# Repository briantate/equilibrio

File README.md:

# equilibrio
A ball balancing project

# Goals:
This is a learning project focused on several learning goals:
* State Space control theory
    * I will start with a simple PID controller, but move to state space control
* Zephyr OS
    * Investigate the west build system 
    * Create a custom board within Zephyr
    * 
* Cloud Connectivity
    * send ball position and other meta data to the cloud
    * Change the balls balancing location from the cloud
    * AWS IoT for the first iteration

# Future goals:
In the future, the following technologies may be added for learning:
* BLE
* Display/graphics
* Capacitive Touch may be investigated as a sensor for ball position

# Block diagram:

# Firmware Architecture:

# Hardware needed:
* Electronics:
    * Adafruit Metro M4 board (later to be a custom board)
    * Custom shield with headers for servo motors, touchscreen sensor, and UART header for console I/O
    * CMSIS-DAP programmer - I'm using Atmel-ICE
    * 2 MG995 180 degree metal gear servo motors
    * 2 Aluminum 25T Servo Horn Steering Arms
    * 2 RC Aluminum Linkages for Servo
    * 1 VSDISPLAY 8.4" 4 wire resistive touchscreen
* Custom balance table hardware
    * 3d-printed table hardware
    * Wooden base board to mount the table hardware

# Zephyr commands needed:
* Install the zephyr ecosystem for your OS following https://docs.zephyrproject.org/latest/develop/getting_started/index.html
* Build: need to be in the embedded_src directory
    > west build -b metro_m4 -p always -- -DBOARD_ROOT=.
    - the -DBOARD_ROOT=. tells west to look for the custom board I created in the current directory (which has the boards subdirectory)
* Flash:
    > west flash

# Notes about design choices:
* Servo:
    * I started with DS-S006L servo’s with plastic gears and plastic steering arms. These seem to work fine, but there is a lot of play in the coupling. Also, the steering arms are not very durable and split with the screws provided
    * I changed out MG995 servo’s with metal gears and steering arms. Hopefully this will reduce some of the play

* Sensor:
    * I'm using a VSDISPLAY 8.4" (172mm x 129.5mm touch area) 4-wire resistive Touch Panel I found on Amazon. I’m looking for larger (and square shaped) panels, but they get expensive quickly with increasing size
        * How 
    * When using an non-square panel, the sensor gains are different in the x and y directions. This is because the voltage drop is across a different distance in each direction, but the ADC range is the same. Ex:
        * 12b ADC = 4096 counts
        * x → 164mm/4096counts = 0.04004mm/count
        * y → 105mm/4096counts = 0x02563mm/count
    * MCU Pin voltage driving the panel lower than 3.3V:
        * The panel resistance is in the range of 300-700 ohms depending on the direction. Typical code examples for Arduino and other platforms drive this sensor with GPIO pins. This is a too much current draw for a typical GPIO pin, so the pin output voltage will drop. You can typically increase the drive strength of a GPIO, but make sure it is enough drive the load or you will measure lower voltages than expected. Ex:
            * typical default drive strength of a MCU GPIO is about 2mA
                * Max load → r=v/i = 1,650 ohms
                * at 300 ohms and 3.3V, → i=v/r = 11mA !!!
                * output pin voltage will droop to where it can actually drive this load
                * v = ir = 0.6V
    * Seeing a strange offset in the sensor reading when no touch is present:
        * The panel some capacitance between the two layers of ITO, and the ADC has some sample capacitance (2-3pF). When you switch on voltage across one layer while the other layer is floating (high impedance into your ADC) and no touch is present, this sensed line voltage will jump to about ½ of the driven voltage and then very slowly decay back to 0. This is because, with no touch, there is very high (almost infinite) resistance between in the sensed line because it’s floating. This causes a large RC time constant. If you sample the line before this decays, you will read the floating voltage instead of the actual voltages
        * My quick solution was to add some pull-down resistance to the sampled lines of the touch panel. I used 5k because I had these in my stock. This does cause a small voltage drop in the reading (but can be accounted for) and significantly speeds up the decay of this voltage, effectively removing the offset from the reading

* Balance table:
    * the play in the servo coupling was accentuated by my initial table design which had the fixed table mount in the middle of the sensing table. This puts the servo load in both tension and compression depending on the position of the ball. If the ball is between the fixed table mount and the servo, the linkage is in compression. If the ball is past the fixed table mount from the servo, the linkage is in tension. When it switches between tension and compression, the play in the linkage causes some error in the actuation of the table. I changed my design to put a fixed table mount on one side of the table, and then put the servo linkage connections at the two opposite corners of the table. This causes the linkage to always be in compression, removing the "transition play"

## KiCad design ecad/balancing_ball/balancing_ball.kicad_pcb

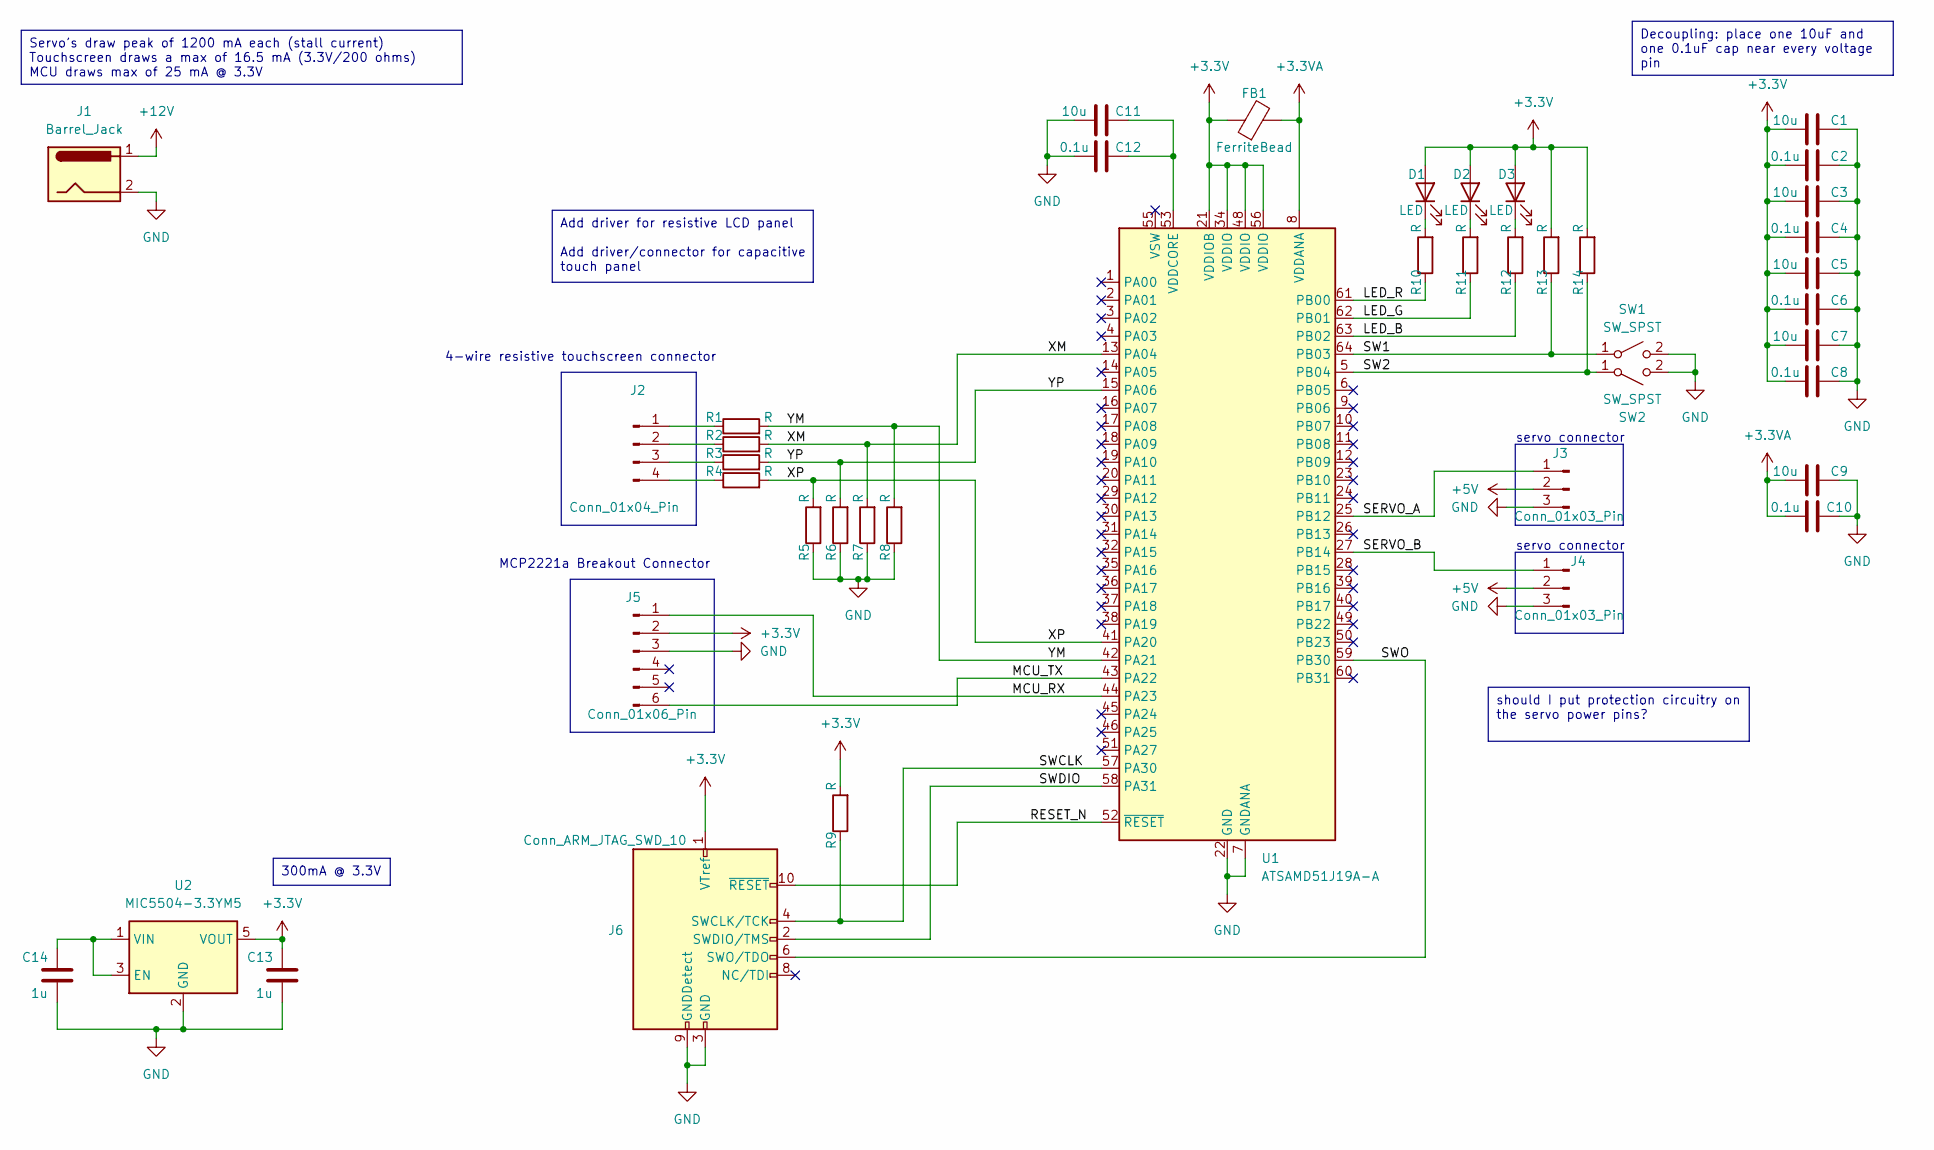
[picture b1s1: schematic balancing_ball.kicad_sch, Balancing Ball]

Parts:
C1, C3, C5, C7, C9, C11: 10u; R_0603_1608Metric
C2, C4, C6, C8, C10, C12: 0.1u; R_0603_1608Metric
C13, C14: 1u; R_0603_1608Metric
D1, D2, D3: LED; D_0603_1608Metric
FB1: FerriteBead; L_0603_1608Metric
J1: Barrel_Jack
J2: Conn_01x04_Pin; PinHeader_1x04_P2.54mm_Horizontal
J3, J4: Conn_01x03_Pin; PinHeader_1x03_P2.54mm_Horizontal
J5: Conn_01x06_Pin; PinHeader_1x06_P2.54mm_Horizontal
J6: Conn_ARM_JTAG_SWD_10; PinSocket_2x05_P1.27mm_Vertical
R1, R2, R3, R4, R5, R6, R7, R8, R9, R10, R11, R12, R13, R14: R; R_0603_1608Metric
SW1, SW2: SW_SPST; SW_Push_1P1T_NO_Vertical_Wuerth_434133025816
U1: ATSAMD51J19A-A; TQFP-64_10x10mm_P0.5mm
U2: MIC5504-3.3YM5; SOT-23-5

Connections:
+3.3V: C1.1, C2.1, C3.1, C4.1, C5.1, C6.1, C7.1, C8.1, C13.1, D1.2 (A), D2.2 (A), D3.2 (A), FB1.1, J5.2, J6.1 (VTref), R9.2, R13.2, R14.2, U1.21 (VDDIOB), U1.34 (VDDIO), U1.48 (VDDIO), U1.56 (VDDIO), U2.5 (VOUT)
+3.3VA: C9.1, C10.1, FB1.2, U1.8 (VDDANA)
+5V: J3.2, J4.2
/LED_B: R12.1, U1.63 (PB02)
/LED_G: R11.1, U1.62 (PB01)
/LED_R: R10.1, U1.61 (PB00)
/MCU_RX: J5.1, U1.44 (PA23)
/MCU_TX: J5.6, U1.43 (PA22)
/RESET_N: J6.10 (~RESET), U1.52 (~RESET)
/SERVO_A: J3.1, U1.25 (PB12)
/SERVO_B: J4.1, U1.27 (PB14)
/SW1: R13.1, SW1.1 (A), U1.64 (PB03)
/SW2: R14.1, SW2.1 (A), U1.5 (PB04)
/SWCLK: J6.4 (SWCLK/TCK), R9.1, U1.57 (PA30)
/SWDIO: J6.2 (SWDIO/TMS), U1.58 (PA31)
/SWO: J6.6 (SWO/TDO), U1.59 (PB30)
/XM: R2.2, R7.2, U1.13 (PA04)
/XP: R4.2, R5.2, U1.41 (PA20)
/YM: R1.2, R8.2, U1.42 (PA21)
/YP: R3.2, R6.2, U1.15 (PA06)
GND: C1.2, C2.2, C3.2, C4.2, C5.2, C6.2, C7.2, C8.2, C9.2, C10.2, C11.1, C12.1, C13.2, C14.2, J1.2, J3.3, J4.3, J5.3, J6.3 (GND), J6.5 (GND), J6.9 (GNDDetect), R5.1, R6.1, R7.1, R8.1, SW1.2 (B), SW2.2 (B), U1.7 (GNDANA), U1.22 (GND), U1.33 (GND), U1.47 (GND), U1.54 (GND), U2.2 (GND)
unnamed: D1.1 (K), R10.2
unnamed: D2.1 (K), R11.2
unnamed: D3.1 (K), R12.2
unnamed: J2.1, R1.1
unnamed: J2.2, R2.1
unnamed: J2.3, R3.1
unnamed: J2.4, R4.1
unnamed: C11.2, C12.2, U1.53 (VDDCORE)
unnamed: C14.1, U2.1 (VIN), U2.3 (EN)

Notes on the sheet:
should I put protection circuitry on the servo power pins?
300mA @ 3.3V
Add driver for resistive LCD panel Add driver/connector for capacitive touch panel
Servo's draw peak of 1200 mA each (stall current) Touchscreen draws a max of 16.5 mA (3.3V/200 ohms) MCU draws max of 25 mA @ 3.3V
Decoupling: place one 10uF and one 0.1uF cap near every voltage pin
MCP2221a Breakout Connector
servo connector
4-wire resistive touchscreen connector

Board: 2 copper layers, 41 parts (0 on the bottom side), 30 nets, no tracks yet.

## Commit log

2025-10-28 add gitignore
2025-10-28 add base project files
2025-10-29 add block diagram and project goals
2025-11-13 add servo's on pb14 and pb15
2025-11-13 add board files for metro_m4
2025-11-13 update TCC channels to 0 and 2
2025-11-14 add video of working balance table
2025-11-14 update servo min and max to match MG995 settings from my previous project
2025-11-17 add adc channel placeholders in the device tree - doesn't compile
2025-11-17 fix overlay - ad address cells and size cells
2025-11-18 add gpio sample code and dt settings
2025-11-18 add back in adc settings in device tree
2025-11-18 update readme with HW design choice details
2025-11-18 move adc and gpio into touch sensor module
2025-11-19 add pid code
2025-11-21 refactor pid code with object pattern
